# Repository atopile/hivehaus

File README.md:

# hivehaus

Collection of avant-garde products for the smart home.

We are using [atopile](https://atopile.io) to design a reusable electronics library for building smart home products. The idea is that most smart home products have the same basic components and can be built with the same tools. 
We are using [esphome](https://esphome.io) to build the firmware for the products.
All pcbs are designed to be manufactured by [JLCPCB](https://jlcpcb.com).

## 📦 Products

- [Hydrohomie](./src/products/hydrohomie) - Scale measuring your water intake per day.

## 🚀 Getting Started

### Prerequisites

- **[atopile](https://docs.atopile.io/atopile/quickstart)** compiler installed
- KiCad 8.0 or later (for PCB viewing/editing)
- Basic SMD soldering equipment

### Building NONOS

1. **Clone the repository**

   ```bash
   git clone https://github.com/atopile/hivehaus
   cd hivehaus/products/<product-name>
   ```

2. **Compile the hardware design**

   ```bash
   ato build
   ```

3. **Generate manufacturing files**

   ```bash
   ato build -t all
   ```

4. **Order PCBs and components**
   - Upload gerbers from `/build` to your preferred PCB manufacturer
   - Use the generated BOM for component ordering

---

## 🤝 Contributing

We love contributions! Whether it's:

- 🐛 Bug fixes
- ✨ New features
- 📚 Documentation improvements
- 🎨 Design enhancements

---

## 📄 License

NONOS is open source hardware, released under the MIT License. See [LICENSE](LICENSE) for details.

---

## 🌟 Acknowledgments

Built with ❤️ using **[atopile](https://atopile.io)** - the language that's revolutionizing hardware design.

Special thanks to the atopile community for making hardware development accessible to everyone.

---

<div align="center">
  
**Ready to build your own smart home products?**

[📖 Read the Docs](https://github.com/atopile/hivehaus) • [💬 Join Discord](https://discord.com/invite/CRe5xaDBr3) • [⭐ Star on GitHub](https://github.com/atopile/hivehaus)

</div>

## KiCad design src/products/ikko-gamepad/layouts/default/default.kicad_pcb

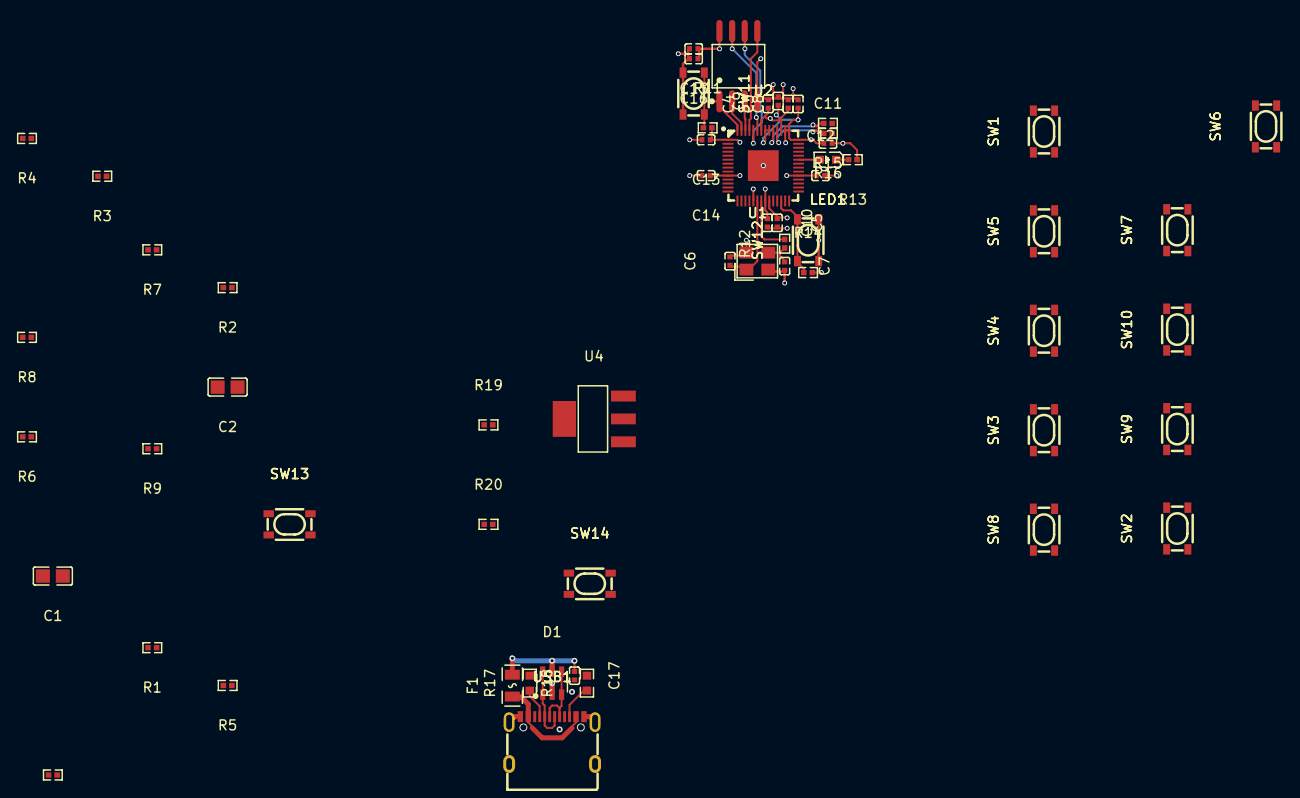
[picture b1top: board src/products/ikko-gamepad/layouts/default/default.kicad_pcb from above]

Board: 2 copper layers, 59 parts (0 on the bottom side), 37 nets.

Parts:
C1, C2: 0F; C0805
C3, C4, C5, C6, C7, C8, C9, C10, C11, C12, C13, C14, C15, C16, C17: 0F; C0402
D1: SOT-23-6_L2.9-W1.6-P0.95-LS2.8-BL
F1: F0805
LED1: LED0603-RD
R1, R2, R3, R4, R5, R6, R7, R8, R9, R10, R11, R13, R14, R19, R20: 10000Ω; R0402
R12: 1000Ω; R0402
R15, R16: 27Ω; R0402
R17, R18: 10000Ω; R0603
SW1, SW2, SW3, SW4, SW5, SW6, SW7, SW8, SW9, SW10, SW11, SW12, SW13, SW14: KEY-SMD_4P-L4.2-W3.2-P2.20-LS4.6
U1: CRYSTAL-SMD_4P-L3.2-W2.5-BL
U2: LQFN-56_L7.0-W7.0-P0.4-EP
U3: SOIC-8_L5.3-W5.3-P1.27-LS8.0-BL
U4: SOT-223-3_L6.5-W3.4-P2.30-LS7.0-BR
USB1: USB-C-SMD_TYPE-C-6PIN-2MD-073

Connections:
4: R17.1, USB1.4
10: R18.1, USB1.10
A: LED1.2, U2.37
CHIP_SELECT: R11.1, SW11.1, SW11.2, U2.56, U3.1
CLOCK: U2.52, U3.6
DATA_0: U2.53, U3.5
DATA_1: U2.55, U3.2
DATA_2: U2.54, U3.3
DATA_3: U2.51, U3.7
DATA_N: R16.2, U2.46
DATA_P: R15.2, U2.47
K: LED1.1, R13.2
RUN: R14.1, SW12.1, SW12.2, U2.26
XIN: C6.1, U1.1, U2.20
XOUT: R12.2, U2.21
_core_regulator_out_power-hv: C3.1, C4.1, C5.1, U2.23, U2.45, U2.50
_core_regulator_out_power-lv: C3.2, C4.2, C5.2, C6.2, C7.2, U1.2, U1.4
gpio[4]-input: R8.2, SW8.1, SW8.2, U2.6
gpio[5]-input: R3.2, SW3.1, SW3.2, U2.7
gpio[6]-input: R4.2, SW4.1, SW4.2, U2.8
gpio[7]-input: R5.2, SW5.1, SW5.2, U2.9
gpio[9]-input: R2.2, SW2.1, SW2.2, U2.12
gpio[10]-input: R9.2, SW9.1, SW9.2, U2.13
gpio[11]-input: R10.2, SW10.1, SW10.2, U2.14
gpio[12]-input: R7.2, SW7.1, SW7.2, U2.15
gpio[13]-input: R6.2, SW6.1, SW6.2, U2.16
gpio[14]-input: R19.2, SW13.1, SW13.2, U2.17
gpio[15]-input: R20.2, SW14.1, SW14.2, U2.18
hv: C2.1, C8.1, C9.1, C10.1, C11.1, C12.1, C13.1, C14.1, C15.1, C16.1, R1.1, R2.1, R3.1, R4.1, R5.1, R6.1, R7.1, R8.1, R9.1, R10.1, R11.2, R14.2, R19.1, R20.1, U2.1, U2.10, U2.22, U2.33, U2.42, U2.43, U2.44, U2.48, U2.49, U3.8, U4.2, U4.4
input: R1.2, SW1.1, SW1.2, U2.11
input-DATA_N: D1.1, D1.6, R16.1, USB1.5, USB1.7
input-DATA_P: D1.3, D1.4, R15.1, USB1.6, USB1.8
lv: C2.2, C8.2, C9.2, C10.2, C11.2, C12.2, C13.2, C14.2, C15.2, C16.2, R13.1, SW1.3, SW1.4, SW2.3, SW2.4, SW3.3, SW3.4, SW4.3, SW4.4, SW5.3, SW5.4, SW6.3, SW6.4, SW7.3, SW7.4, SW8.3, SW8.4, SW9.3, SW9.4, SW10.3, SW10.4, SW11.3, SW11.4, SW12.3, SW12.4, SW13.3, SW13.4, SW14.3, SW14.4, U2.19, U2.57, U3.4
power-hv: C7.1, R12.1, U1.3
power_in-hv: C1.1, C17.1, D1.5, F1.2, U4.3
power_in-lv: C1.2, C17.2, D1.2, R17.2, R18.2, U4.1, USB1.1, USB1.12, USB1.13, USB1.14, USB1.15, USB1.16
power_vbus-hv: F1.1, USB1.2, USB1.11

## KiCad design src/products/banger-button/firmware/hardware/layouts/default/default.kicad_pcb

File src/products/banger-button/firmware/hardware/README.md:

# Banger Button
## Description
Have you ever been in this situation...

## Features
- **The Button** with Built-in OLED Display and Rotary Encoder
- 4x Multi-purpose Buttons
- 4x Motorized Faders
- Multi-button Synchronization and Conflict Resolution
- Integrate with Rekordbox to automatically save Bangers™️ to USB

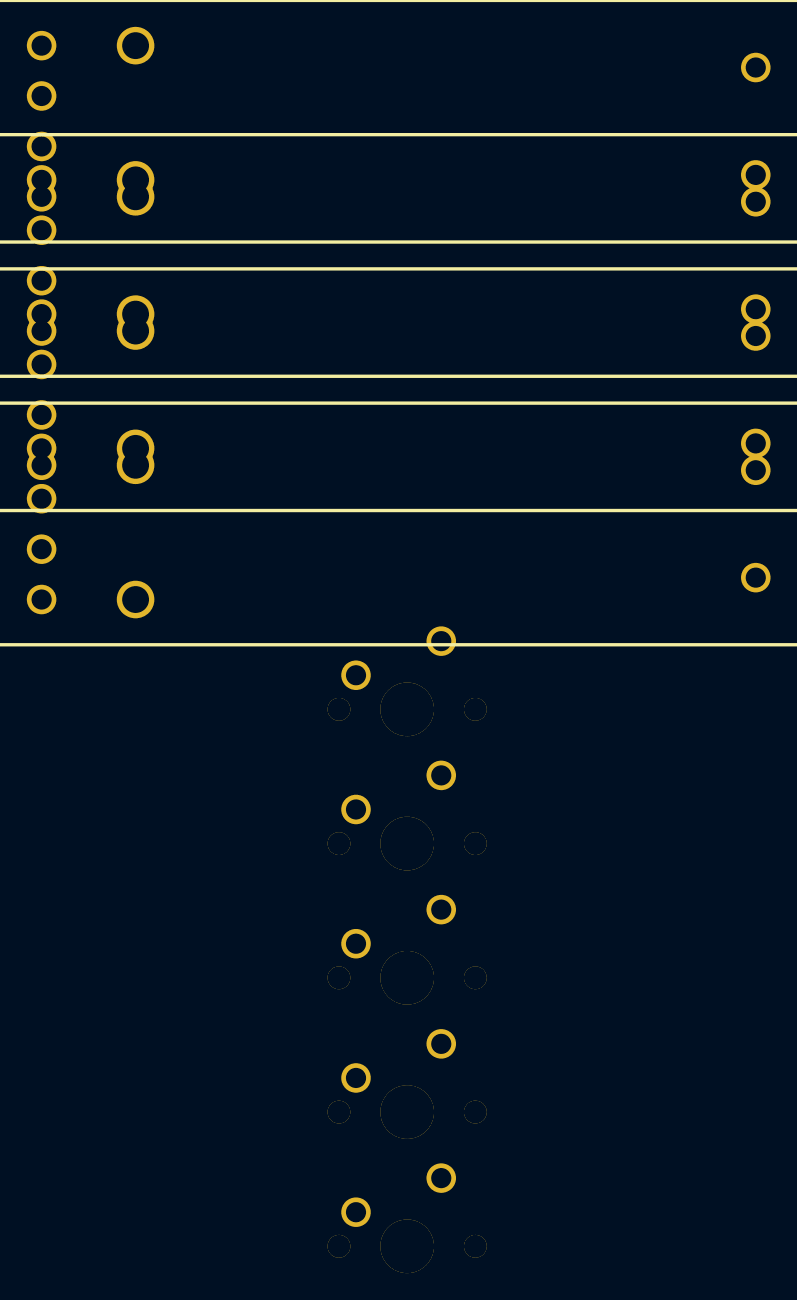
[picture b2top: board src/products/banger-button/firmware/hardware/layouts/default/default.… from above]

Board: 2 copper layers, 9 parts (0 on the bottom side), 4 nets, no tracks yet.

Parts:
R1, R2, R3, R4: RES-ADJ-TH_RS60N11M9A0F
SW1, SW2, SW3, SW4, SW5: SW-TH_MX1A-11NW

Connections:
faders[0]-L: R1.L1, R1.L2
faders[1]-L: R2.L1, R2.L2
faders[2]-L: R3.L1, R3.L2
faders[3]-L: R4.L1, R4.L2

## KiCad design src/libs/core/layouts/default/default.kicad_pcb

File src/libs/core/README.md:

# Hivehaus Core

An ato library module containing the microcontroller and required infrastructure that all Hivehaus products import and build upon.

## 📋 Specification

### Overview
The Hivehaus Core is a reusable ato library module that products import to get the common foundation needed for all Hivehaus smart home products. When a product imports the Core, it gets a complete ESP32-C3 subsystem with power management, wireless connectivity, and standardized interfaces ready to connect to product-specific peripherals.

### Architecture Principles
- **Single PCB Design**: Products import Core as a library, everything on one board
- **Modularity**: Core functions cleanly separated from product-specific features
- **ESPHome First**: Designed for ESPHome configuration and management
- **Manufacturing**: Optimized for JLCPCB assembly with common parts
- **Consistency**: All products share the same core architecture

## 🔧 Components

### 1. Microcontroller
- **ESP32-C3-MINI-1** module
  - WiFi 2.4GHz (802.11 b/g/n)
  - Bluetooth 5.0 LE
  - 4MB Flash (integrated)
  - 400KB SRAM
  - RISC-V single-core 160MHz
  - 40MHz crystal (integrated)

### 2. Power System
- **USB-C**: Always present for programming and default power
- **Power Supply Module**: Default LDO module (can be retyped)
  - Input: VBUS from USB-C
  - Output: 5V and 3.3V rails
- **Protection**: ESD on USB and exposed interfaces
- **Extensible**: Products can retype `core.power_supply` module

### 3. User Interface
- **Buttons**:
  - BOOT button (GPIO9) - Also usable as user input after boot
  - RESET button (EN pin)
- **LEDs**:
  - Power LED (connected directly to 3.3V rail with resistor)
  - Status LED (SK6805 addressable RGB LED with data line on GPIO9, exposed on HiveIO.led_data)

### 4. Debug & Programming
- **USB Serial/JTAG**: Built-in ESP32-C3 USB controller (no external chip needed)
  - GPIO18: USB D-
  - GPIO19: USB D+
- **Debug Header**: 10-pin Saleae-compatible on breakaway tab
  - I2C test points
  - SPI test points
  - Power monitoring points
- **Test Points**: Key signals accessible for probing

### 5. Expansion Interfaces
- **HiveIO**: Flexible interface for product-specific needs
  - I2C (GPIO5/6): Shared I2C bus (package default pins)
  - SPI (GPIO7/8/10): SPI bus - MOSI/MISO/SCLK (package defaults)
  - UART (GPIO20/21): Hardware UART - RX/TX
  - GPIO0: ADC capable, general IO
  - GPIO1: ADC capable, general IO
  - GPIO2: ADC capable, general IO (boot strap pin)
  - GPIO3: ADC capable, general IO
  - GPIO4: ADC capable, general IO
  - LED Data (GPIO9): Data output from addressable RGB LED (can be chained or reassigned)
- **HiveExpansion Connector**:
  - STEMMA QT / Qwiic compatible (same as Adafruit/SparkFun standard)
  - I2C interface (connected to shared I2C bus from HiveIO)
  - 3.3V power and ground
  - JST-SH 4-pin connector (standard pinout: GND, 3V3, SDA, SCL)

## 📌 ESP32-C3-MINI-1 Pin Mapping

### Complete GPIO Allocation
| GPIO | Core Usage | HiveIO Access | Package Pin Name | Notes |
|------|------------|---------------|------------------|-------|
| GPIO0 | Free | ✅ io0 | IO0 | ADC1_CH0 |
| GPIO1 | Free | ✅ io1 | IO1 | ADC1_CH1 |
| GPIO2 | Free | ✅ io2 | IO2 | ADC1_CH2, Boot strap |
| GPIO3 | Free | ✅ io3 | IO3 | ADC1_CH3 |
| GPIO4 | Free | ✅ io4 | IO4 | ADC1_CH4, JTAG TMS |
| GPIO5 | I2C SDA | ✅ i2c | IO5 | ADC2_CH0, I2C default |
| GPIO6 | I2C SCL | ✅ i2c | IO6 | I2C default, JTAG TCK |
| GPIO7 | SPI MOSI | ✅ spi | IO7 | SPI default, JTAG TDO |
| GPIO8 | SPI MISO | ✅ spi | IO8 | SPI default, Boot strap |
| GPIO9 | RGB LED Data | ✅ led_data | IO9 | Addressable LED data out |
| GPIO10 | SPI SCLK | ✅ spi | IO10 | SPI default |
| GPIO11-17 | Not Available | ❌ | - | Internal SPI Flash |
| GPIO18 | USB D- | ❌ Core | IO18 | USB_D- |
| GPIO19 | USB D+ | ❌ Core | IO19 | USB_D+ |
| GPIO20 | UART TX | ✅ uart | TXD0 | U0TXD |
| GPIO21 | UART RX | ✅ uart | RXD0 | U0RXD |

Note: The ESP32_C3_MINI_1_driver in the package also includes:
- Boot and reset buttons with debounce capacitors
- Boot mode pull-up resistors on GPIO2 and GPIO8
- Reset pull-up resistor on EN pin
- Decoupling capacitors (22µF bulk + 100nF)

### Boot Strapping Pins
- **GPIO2**: Floating (SPI boot by default)
- **GPIO8**: Floating or HIGH for SPI boot
- **GPIO9**: HIGH for normal boot, LOW for download mode

## 📐 Design Guidelines for Products

### When Using the Core
Products that import the Core module should follow these guidelines:

### Required Board Area
- **ESP32-C3-MINI-1 Module**: 13.2mm x 16.6mm x 2.4mm (height)
- **Core Section Total**: Reserve ~20x20mm for module and support components
- **Antenna Keepout**: 15x7mm keepout area for PCB antenna (no copper on any layer)
- **USB Section**: Reserve space for USB-C connector at board edge
- **Debug Section**: Optional breakaway tab (10x30mm) for debug header

### Important Design Notes
- **ESP32-C3-MINI-1**: Has integrated 40MHz crystal and 4MB flash
- **Boot Strapping**: GPIO2, GPIO8, GPIO9 have boot-time functions (handled by Core)
- **Ground Plane**: Solid ground plane recommended under ESP32 module
- **Decoupling**: Place 100nF caps close to each VDD pin

### Standard Connectors
- **USB-C**: Included in Core for power and programming (can be retyped)
- **JST-SH 4-pin**: HiveExpansion (STEMMA QT/Qwiic compatible)
  - Pin 1: GND (Black wire)
  - Pin 2: 3.3V (Red wire)
  - Pin 3: SDA (Blue wire)
  - Pin 4: SCL (Yellow wire)
- **Debug Header**: 10-pin 0.1" header on breakaway section (optional)

## 🔌 Module Interfaces

### What Products Get When Importing Core

```ato
from "hivehaus/core/main.ato" import Core

module MyProduct:
    # Instantiate the core (includes USB-C and default LDO power supply)
    core = new Core
    
    # Use the exposed interfaces
    my_sensor.i2c ~ core.expansion.i2c
    my_button ~ core.hiveio.io0
    
    # Example: Replace power supply with battery management
    # from "packages/battery-manager.ato" import BatteryPowerSupply
    # core.power_supply -> BatteryPowerSupply
```

### Exposed Interfaces from Core Module

```ato
module Core:
    # Microcontroller
    mcu = new ESP32_C3_MINI_1_driver
    
    # USB-C always present (for programming and power)
    usb = new USBCConn      # Always populated, never retyped
    
    # Power supply module (can be retyped by products)
    power_supply = new DefaultPowerSupply
    
    # Power rails (outputs from power_supply)
    power_5v = new ElectricPower     # 5V ±5%
    power_3v3 = new ElectricPower    # 3.3V ±5%
    
    # Internal connections:
    # usb.power ~ power_supply.vbus_in
    # usb.dp ~ mcu.GPIO19  # USB D+ direct to ESP32-C3
    # usb.dm ~ mcu.GPIO18  # USB D- direct to ESP32-C3
    # power_supply.power_5v ~ power_5v
    # power_supply.power_3v3 ~ power_3v3
    # power_3v3 ~ mcu.power
    
    # Internal: RGB LED controller on shared I2C bus (GPIO4/5)
    
    # Product interfaces via HiveIO
    hiveio = new HiveIO     # All product-accessible interfaces
    
    # STEMMA QT/Qwiic expansion
    expansion = new HiveExpansion  # I2C from HiveIO + 3.3V power

# Base power supply interface that all implementations must follow
module HiveCorePowerSupply:
    vbus_in = new ElectricPower   # Input from USB-C VBUS
    power_5v = new ElectricPower  # 5V output rail
    power_3v3 = new ElectricPower # 3.3V output rail

# Default implementation: Simple LDO from USB
module DefaultPowerSupply from HiveCorePowerSupply:
    # Internal: Pass-through 5V from USB
    # Internal: LDO regulator 5V to 3.3V

interface HiveIO:
    # Shared I2C bus (products and Core RGB LED controller)
    i2c = new I2C           # GPIO5/6 (SDA/SCL - package defaults)
    
    # Product SPI bus  
    spi = new SPI           # GPIO7/8/10 (MOSI/MISO/SCLK - package defaults)
    
    # Product UART bus
    uart = new UART         # GPIO20/21 (RX/TX - package defaults)
    
    # Flexible GPIOs (all ADC capable)
    io0 = new ElectricLogic # GPIO0 - ADC1_CH0
    io1 = new ElectricLogic # GPIO1 - ADC1_CH1
    io2 = new ElectricLogic # GPIO2 - ADC1_CH2, boot strap
    io3 = new ElectricLogic # GPIO3 - ADC1_CH3
    io4 = new ElectricLogic # GPIO4 - ADC1_CH4
    
    # Power reference
    power = new ElectricPower

interface HiveExpansion:
    i2c = new I2C               # Same as hiveio.i2c (GPIO5/6)
    power = new ElectricPower   # 3.3V for STEMMA QT/Qwiic devices
```

### Internal Core Connections (Handled Automatically)
- ESP32-C3-MINI-1 module with all power/ground
- USB-C connector (always present) with ESD protection
- USB data lines direct to ESP32-C3 (GPIO18/19)
- Power supply module (default: LDO, retypeable)
- BOOT button on GPIO9
- RESET button on EN
- Pull-up resistors on I2C buses
- Decoupling capacitors

### Power Supply Interface Contract
All power supply modules must inherit from `HiveCorePowerSupply`:
- `vbus_in`: Input from USB-C VBUS
- `power_5v`: 5V output rail  
- `power_3v3`: 3.3V output rail

This ensures retype compatibility and consistent interfaces.

## 🔄 Power Architecture Flexibility

### Default Power Configuration
The Core has a two-tier power architecture:
- **USB-C connector**: Always present for programming and default power
- **Power Supply Module**: Default LDO implementation (retypeable)
- **Power outputs**: 5V and 3.3V rails available to products

### Customizing Power Architecture
Products retype `core.power_supply` to change power management:

```ato
# Battery Power Supply Module  
module BatteryPowerSupply from HiveCorePowerSupply:
    # Inherited: vbus_in, power_5v, power_3v3
    
    # Internal components
    charger = new BatteryCharger
    battery = new LiPoBattery
    power_mux = new PowerMux
    ldo_3v3 = new LDO_3V3
    
    # Internal connections
    vbus_in ~ charger.vbus
    charger.vbat ~ battery.power
    charger.vsys ~ power_mux.input_a
    battery.power ~ power_mux.input_b
    power_mux.output ~ power_5v
    power_5v ~ ldo_3v3.vin
    ldo_3v3.vout ~ power_3v3

# Using in a product
module BatteryProduct:
    core = new Core
    core.power_supply -> BatteryPowerSupply
```

```ato
# Buck Converter Power Supply (for higher voltage input)
module BuckPowerSupply from HiveCorePowerSupply:
    # Inherited: vbus_in, power_5v, power_3v3
    
    # Additional input for high voltage
    vin_high = new ElectricPower   # 12-24V input
    
    # Buck converters
    buck_5v = new BuckConverter_5V
    buck_3v3 = new BuckConverter_3V3
    
    # Use high voltage input, ignore USB
    vin_high ~ buck_5v.vin
    buck_5v.vout ~ power_5v
    vin_high ~ buck_3v3.vin  
    buck_3v3.vout ~ power_3v3

# Product with external power
module HighVoltageProduct:
    core = new Core
    core.power_supply -> BuckPowerSupply
    
    # Connect external power
    barrel_jack = new DCBarrelJack
    barrel_jack.power ~ core.power_supply.vin_high
```

### Power States
- **Active**: Full operation, WiFi/BT active (~80mA)
- **Light Sleep**: CPU idle, peripherals active (~15mA)
- **Deep Sleep**: RTC only (<10µA)
- **Power control**: Managed via ESPHome configuration

## 🧪 Test Strategy

### Manufacturing Tests
- Boundary scan for connectivity
- Power rail validation
- RF performance verification
- Flash programming verification

### Functional Tests
- WiFi/Bluetooth connectivity
- USB enumeration and data transfer
- GPIO functionality
- Sleep mode current consumption

## 📊 Performance Targets

- **Power Consumption**:
  - Active WiFi: <80mA @ 3.3V
  - BLE advertising: <15mA @ 3.3V
  - Deep sleep: <10µA
- **Boot Time**: <2 seconds to user code
- **WiFi Range**: >20m indoor typical
- **Operating Temp**: -20°C to +70°C

## 🏭 Manufacturing Considerations

- **Assembly**: Single-sided placement preferred
- **Components**: JLCPCB basic/preferred parts where possible
- **Testability**: Built-in self-test firmware
- **Panelization**: V-score compatible design

## 🏠 ESPHome Integration

### Base Configuration Template
```yaml
esphome:
  name: hivehaus-core
  platform: ESP32
  board: esp32-c3-devkitm-1

wifi:
  ssid: !secret wifi_ssid
  password: !secret wifi_password

api:
  encryption:
    key: !secret api_encryption_key

ota:
  password: !secret ota_password

# Single I2C bus (shared by Core and products)
i2c:
  id: i2c_bus
  sda: GPIO5
  scl: GPIO6
  scan: true
  frequency: 100kHz

# Core status LED (I2C RGB controller on shared bus)
light:
  - platform: pca9685
    id: rgb_controller
    address: 0x60  # Fixed address for Core RGB LED
    i2c_id: i2c_bus
    
  - platform: rgb
    name: "Status LED"
    red: rgb_controller_0
    green: rgb_controller_1
    blue: rgb_controller_2

# SPI bus (package defaults)
spi:
  clk_pin: GPIO10
  mosi_pin: GPIO7
  miso_pin: GPIO8

# Product UART (package defaults)
uart:
  tx_pin: GPIO21
  rx_pin: GPIO20
  baud_rate: 115200

# Flexible HiveIO pins (product-specific)
# All 5 GPIOs available for any use
binary_sensor:
  - platform: gpio
    pin: GPIO0
    name: "HiveIO Input 0"
    
output:
  - platform: gpio
    pin: GPIO1
    id: hiveio_output_1
    
sensor:
  - platform: adc
    pin: GPIO2
    name: "HiveIO ADC 2"
    attenuation: 11db
  - platform: adc
    pin: GPIO3
    name: "HiveIO ADC 3"
    attenuation: 11db
  - platform: adc
    pin: GPIO4
    name: "HiveIO ADC 4"
    attenuation: 11db
```

### Fixed Pin Assignments
Core reserved pins (not accessible to products):
- **GPIO18/19**: USB Serial/JTAG (built-in USB programming)
- **GPIO9**: BOOT button

### Product Accessible Pins (via HiveIO)
- **GPIO5/6**: I2C bus (SDA/SCL - shared with Core RGB LED at address 0x60)
- **GPIO7/8/10**: SPI bus (MOSI/MISO/SCLK)
- **GPIO20/21**: UART bus (RX/TX)
- **GPIO0-4**: 5 flexible GPIOs (all ADC capable)

### STEMMA QT/Qwiic Compatibility
The HiveExpansion connector follows the standard pinout used by:
- Adafruit STEMMA QT
- SparkFun Qwiic
- Grove (with adapter)

This allows direct connection to thousands of existing I2C sensors and modules without custom adapters.

### Power Management in ESPHome
```yaml
# Deep sleep configuration
deep_sleep:
  run_duration: 60s
  sleep_duration: 5min
  wakeup_pin: GPIO9  # BOOT button as wake source
```

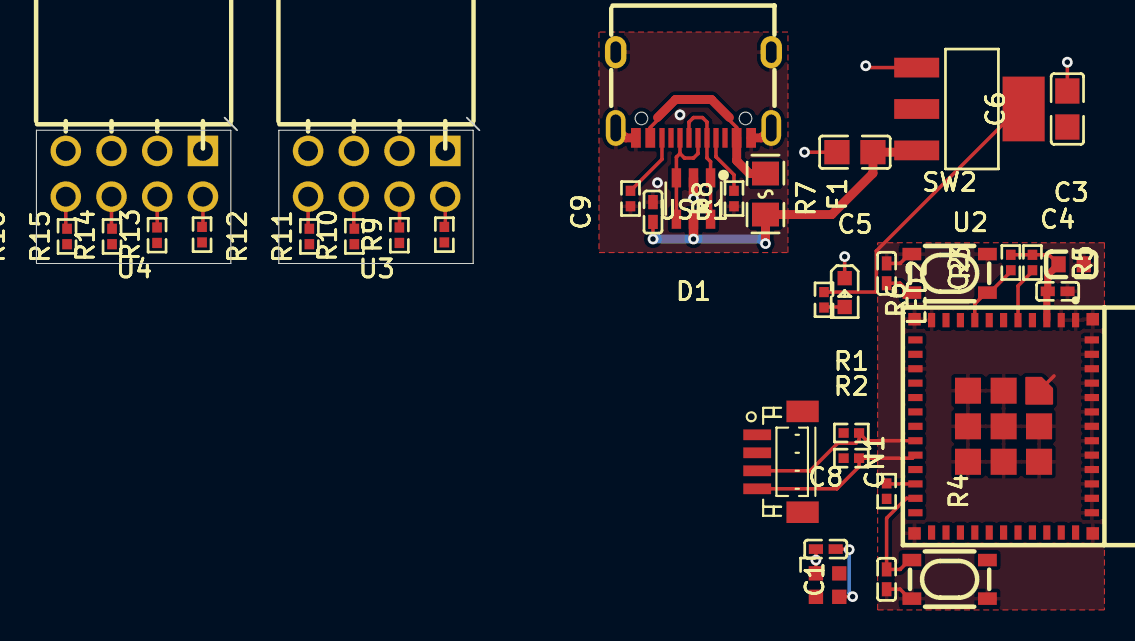
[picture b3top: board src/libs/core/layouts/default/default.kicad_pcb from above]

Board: 2 copper layers, 24.6 x 8.1 mm, 36 parts (0 on the bottom side), 26 nets.

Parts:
C1, C2, C4, C8, C9: 100nF ±10% 16V X7R; C0402
C3: 22µF ±20% 6.3V X5R; C0603
C5: 10µF ±10% 25V X5R; C0805
C6: 22µF ±20% 6.3V X5R; C0805
CN1: CONN-SMD_BM04B-SRSS-TB
D1: SOT-23-6_L2.9-W1.6-P0.95-LS2.8-BL
F1: F0805
LED1: LED-SMD_4P-L2.0-W2.0-BR
LED2: LED0603-RD
R1, R2: 4.7kΩ ±1% 62.5mW; R0402
R3, R4, R5: 10kΩ ±1% 62.5mW; R0402
R6, R9, R10, R11, R12, R13, R14, R15, R16: 1kΩ ±1% 62.5mW; R0402
R7, R8: 5.1kΩ ±1% 62.5mW; R0402
SW1, SW2: KEY-SMD_4P-L4.2-W3.2-P2.20-LS4.6
U1: WIFIM-SMD_ESP32-C3-MINI-1
U2: SOT-223-3_L6.5-W3.4-P2.30-LS7.0-BR
U3, U4: HDR-TH_8P-P2.54-H-F-R2-C4-W8.5
USB1: USB-C-SMD_TYPE-C-6PIN-2MD-073

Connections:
-hv: C5.1, C9.1, D1.5, F1.2, R14.1, U2.3
-line-0: CN1.3, R1.2, R9.1, U1.19
-line-1: CN1.4, R2.2, R10.1, U1.20
-line-2: LED1.2, R11.1
-line-3: R12.1, U1.12
-line-5: R3.1, U1.5
-line-8: R4.1, U1.22
anode: LED2.2, R6.2
debug_header.headers[0]-_2: R9.2, U3.2
debug_header.headers[0]-_4: R10.2, U3.4
debug_header.headers[0]-_6: R11.2, U3.6
debug_header.headers[0]-_8: R12.2, U3.8
debug_header.headers[1]-_2: R13.2, U4.2
debug_header.headers[1]-_4: R14.2, U4.4
debug_header.headers[1]-_6: R15.2, U4.6
debug_header.headers[1]-_8: R16.2, U4.8
debug_header.headers[1]-gnd: U4.1, U4.3, U4.5, U4.7
gnd: C1.1, C2.1, C3.2, C4.2, C5.2, C6.2, C8.2, C9.2, CN1.1, D1.2, LED1.3, LED2.1, R7.2, R8.2, SW1.1, SW1.2, SW2.1, SW2.2, U1.1, U1.2, U1.11, U1.14, U1.36, U1.37, U1.38, U1.39, U1.40, U1.41, U1.42, U1.43, U1.44, U1.45, U1.46, U1.47, U1.48, U1.49, U1.50, U1.51, U1.52, U1.53, U2.1, U3.1, U3.3, U3.5, U3.7, USB1.1, USB1.12, USB1.13, USB1.14, USB1.15, USB1.16
hv-0: F1.1, USB1.2, USB1.11
hv-1: C3.1, C4.1, C6.1, C8.1, CN1.2, LED1.1, R1.1, R2.1, R3.2, R4.2, R5.1, R6.1, R13.1, U1.3, U2.2, U2.4
line-0: R7.1, USB1.4
line-1: R8.1, USB1.10
line-4: D1.1, D1.6, U1.26, USB1.5, USB1.7
line-5: D1.3, D1.4, U1.27, USB1.6, USB1.8
output-0: C1.2, LED1.4, SW1.3, SW1.4, U1.23
output-1: C2.2, R5.2, SW2.3, SW2.4, U1.8

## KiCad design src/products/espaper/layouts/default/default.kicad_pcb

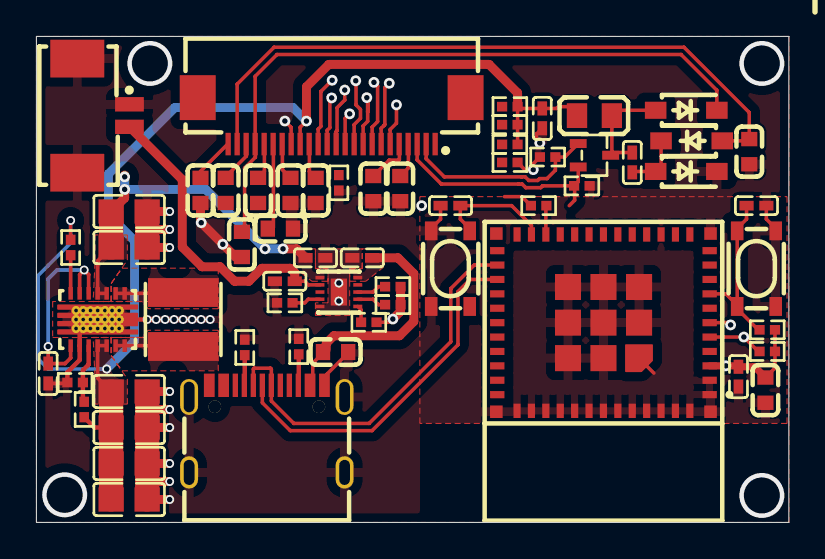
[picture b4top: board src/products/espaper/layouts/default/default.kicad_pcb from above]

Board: 2 copper layers, 41.8 x 27.0 mm, 61 parts (1 on the bottom side), 42 nets.

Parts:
B1: EEMB_BATTERY_LP402535
C1: 4.7µF ±20% 10V X5R; C0402
C2, C5, C6, C7, C8, C9, C10, C11, C12, C13: 1µF ±10% 50V X5R; C0603
C3, C4: 10µF ±10% 25V X5R; C0805
C14, C15, C17, C24: 100nF ±10% 16V X7R; C0402
C16: 22µF ±20% 6.3V X5R; C0603
C18, C25, C27: 1µF ±10% 25V X5R; C0402
C19: 4.7µF ±10% 16V X5R; C0603
C20, C21, C22, C23: 22µF ±20% 6.3V X5R; C0805
C26: 10µF ±20% 6.3V X5R; C0402
D1, D2, D3: SOD-123_L2.7-W1.6-LS3.7-RD-1
FPC1: FPC-SMD_24P-P0.50_FPC-05F-24PH20
L1: 1µH ±20% 4.7A 18mΩ; IND-SMD_L4.0-W4.0_FNR40XXS
L2: 68µH ±10% 9MHz 2mA 2Ω; L0805
Q1: SOT-323-3_L2.0-W1.3-P1.30-LS2.1-BR
R1: 180kΩ ±1% 62.5mW; R0402
R2, R5: 1MΩ ±1% 62.5mW; R0402
R3: 3.3Ω ±1% 62.5mW; R0402
R4, R6, R7, R8, R9, R11, R12, R16, R18, R19: 10kΩ ±1% 62.5mW; R0402
R10: 470mΩ ±1% 62.5mW; R0402
R13, R14: 4.7kΩ ±1% 62.5mW; R0402
R15: 2kΩ ±1% 62.5mW; R0402
R17: 18kΩ ±1% 62.5mW; R0402
SW1, SW2: KEY-SMD_4P-L4.2-W3.2-P2.20-LS4.6
U1: CONN-SMD_532610271
U2: WIFIM-SMD_ESP32-C3-MINI-1
U3: VSON-14_L4.0-W3.0-P0.50-BL-EP_TI_DSJ
U4: WSON-10_L2.2-W2.0-P0.40-BL-EP_TI_DLH0010A
USB1: USB-C-SMD_KH-TYPE-C-16P

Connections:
-anode-0: C18.1, D1.2, D3.1
-anode-1: C12.1, D3.2, FPC1.23
-hv-0: C25.1, U1.2, U4.2
-hv-1: C1.1, C16.1, C17.1, C20.1, C21.1, C22.1, C23.1, FPC1.16, L2.1, R2.1, R4.2, R5.2, R6.2, R7.2, R8.2, R9.1, R12.2, U2.3, U3.4, U3.5
-hv-2: C19.1, C27.1, U4.10, USB1.A4, USB1.A9, USB1.B4, USB1.B9
-line-0: FPC1.8, R3.1
-line-1: FPC1.9, R4.1, R7.1, U2.5
-line-2: FPC1.12, R18.1
-line-3: FPC1.11, R6.1, U2.18
-line-4: C5.1, FPC1.4
-line-5: C6.1, FPC1.5
-line-6: C7.1, FPC1.18
-line-7: C8.1, FPC1.19
-line-8: C9.1, FPC1.20
-line-9: C11.1, FPC1.22
-line-10: C13.1, FPC1.24
-line-11: FPC1.10, R12.1, U2.6
-line-12: FPC1.13, U2.16
-line-13: FPC1.14, U2.21
-line-14: R8.1, U2.22
-line-15: U2.26, USB1.A7, USB1.B7
-line-16: U2.27, USB1.A6, USB1.B6
A5: R13.1, USB1.A5
B5: R14.1, USB1.B5
EN: C24.1, U3.1, U3.12, U3.13
FB: R1.1, R2.2, U3.3
ILIM_VSET: R17.1, U4.7
ISET: R15.1, U4.8
L1: L1.1, U3.8, U3.9
L2: L1.2, U3.6, U3.7
PG: R5.1, U3.14
TS_MR: R19.1, U4.6
VIN: C3.1, C4.1, C26.1, U3.10, U3.11, U4.1
cathode: C10.1, D2.1, FPC1.21
gate: FPC1.2, Q1.1, R11.1
gnd: C1.2, C2.2, C3.2, C4.2, C5.2, C6.2, C7.2, C8.2, C9.2, C10.2, C11.2, C12.2, C13.2, C14.1, C15.1, C16.2, C17.2, C19.2, C20.2, C21.2, C22.2, C23.2, C24.2, C25.2, C26.2, C27.2, D1.1, FPC1.17, R1.2, R3.2, R10.2, R11.2, R13.2, R14.2, R15.2, R16.2, R17.2, R18.2, R19.2, SW1.1, SW1.2, SW2.1, SW2.2, U1.1, U1.3, U1.4, U2.1, U2.2, U2.11, U2.14, U2.36, U2.37, U2.38, U2.39, U2.40, U2.41, U2.42, U2.43, U2.44, U2.45, U2.46, U2.47, U2.48, U2.49, U2.50, U2.51, U2.52, U2.53, U3.2, U3.15, U4.5, U4.11, USB1.1, USB1.2, USB1.3, USB1.4, USB1.A1, USB1.A12, USB1.B1, USB1.B12
nCE: R16.1, U4.4
output-0: C14.2, SW1.3, SW1.4, U2.23
output-1: C15.2, R9.2, SW2.3, SW2.4, U2.8
source: FPC1.3, Q1.2, R10.1
sw_node: C18.2, D2.2, L2.2, Q1.3
vddio: C2.1, FPC1.15

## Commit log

2025-08-08 Init commit
2025-08-08 setup structure
2025-08-08 add agents.md for codex
2025-08-08 fix workflow
2025-08-08 Libs: Core: Add boilerplate
2025-08-08 spec
2025-08-08 plan
2025-08-08 Doc: Readme fix
2025-08-08 has_esphome_config_from_template
2025-08-09 first stab at espaper
2025-08-09 fix substitutions
2025-08-09 external build target
2025-08-09 include exporter
2025-08-09 migrate traits
2025-08-09 almost done, need to finish a few traces
2025-08-09 good base
2025-08-09 trait from package
2025-08-22 shipped espaper on jlc
2025-10-06 Init test firmware for epaper
2025-10-11 ESPHome firmware
2025-10-13 espaper: automatic workout schedule WIP
2025-10-17 Auto updates for circuit 1 working
2025-10-17 Add circuit 2 workouts
2025-10-17 daily offsets working
2025-10-17 Use real time and display update every minute, still need to fix update information before display update (off by 1 minute)
2025-10-22 Fixed the display lagging by 1 minute
2025-11-07 latest
2026-01-27 update packages deps
2026-03-03 init
